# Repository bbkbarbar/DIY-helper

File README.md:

# DIY-helper
..is a arduino based distance meter tool <br> with 4 distance sensors looks "up", "down", left and right, to help positioning things on the wall (e.g.: picture frames) or on the floor.

[The original idea found on this video.](https://youtu.be/QvjQSEvRNkw)

### Planned features:

 - Simple distance measurement
 - Distance measurement in 2 opposite side (can select direction [left-right / up-down])
 - Positioning: continously show the distance values in real time (measure from middle hole or from the side)
    - Can "store" the position and measure distance from that point
 - Area calculation (can select display unit (cm2 or m2 -usefull for wall painting-))

### Used libraries:
 - For handling more push-buttons on 1 single ADC input: [ButtonHandler-library](https://bbkbarbar.github.io/Arduino-ButtonHandler-library/)
 - For handling OLED display over softSpi bus: [SSD1306Ascii-library](https://bbkbarbar.github.io/Arduino-SSD1306Ascii/)
 - For handling HC-SR04 distance sensor: [HC-SR04 library](https://bbkbarbar.github.io/Arduino-HC-SR04-library/)

### Custom modules:
 - Main board (as arduino nano shield) [schematic](https://github.com/bbkbarbar/DIY-helper/blob/master/Docs/mail_board.png), [pcb design](https://github.com/bbkbarbar/DIY-helper/blob/master/Docs/mail_board_pcb.png), [pcb design as .pdf](https://github.com/bbkbarbar/DIY-helper/raw/master/Eagle/DIY_tool_-_Arduino_nano_shield_pcb_v1.1.pdf)
 - Button board [schematic](https://github.com/bbkbarbar/DIY-helper/blob/master/Docs/button_board.png), [pcb design](https://github.com/bbkbarbar/DIY-helper/blob/master/Docs/button_board_pcb.png), [pcb design as .pdf](https://github.com/bbkbarbar/DIY-helper/raw/master/Eagle/DIY_tool_-_button_panel_pcb_v1.pdf)

### ToDo list:
- [x] Clarify / finalyze planned features
- [x] Create test circuits on bread-boards for handling multiple buttons on 1 ADC input
- [x] Try out to use multiple buttons in 1 ADC line
- [x] Create schematic for main board
- [x] Create schematic for button board according to the planned features (e.g.: count of push-buttons)
- [x] Create PCB design for main board
- [x] Create PCB design for button board
- [ ] Finalyze part-list and buy missing parts (if there any)
- [ ] Create test circuits on bread-boards for complete project
- [ ] Create plans for "UI"
- [ ] Create the "RC"-version from firmware
- [ ] <b>After first working bread-board prototype:</b>
- [ ] Create case-design
- [ ] Decide about used materials
- [ ] Build final version in proper case.

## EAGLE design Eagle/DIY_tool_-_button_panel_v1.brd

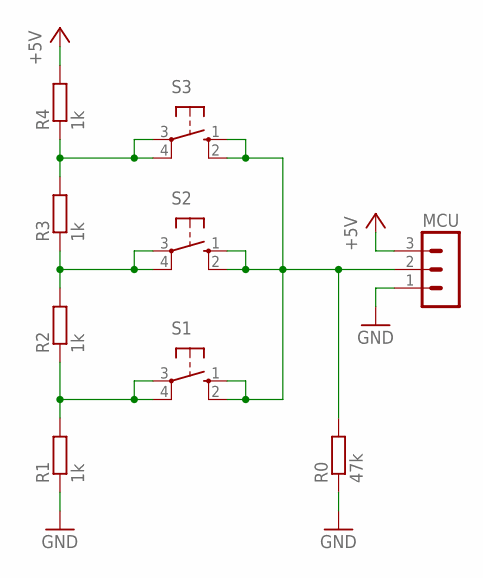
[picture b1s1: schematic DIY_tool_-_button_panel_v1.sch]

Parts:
MCU: MA03-1
R0: 47k; 0207/10
R1, R2, R3, R4: 1k; 0207/10
S1, S2, S3: 10-XX; B3F-10XX

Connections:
+5V: MCU.3, R4.2
ADC: MCU.2, R0.2, S1.1 (S), S1.2 (S1), S2.1 (S), S2.2 (S1), S3.1 (S), S3.2 (S1)
B1: R1.2, R2.1, S1.3, S1.4 (P1)
B2: R2.2, R3.1, S2.3, S2.4 (P1)
B3: R3.2, R4.1, S3.3, S3.4 (P1)
GND: MCU.1, R0.1, R1.1

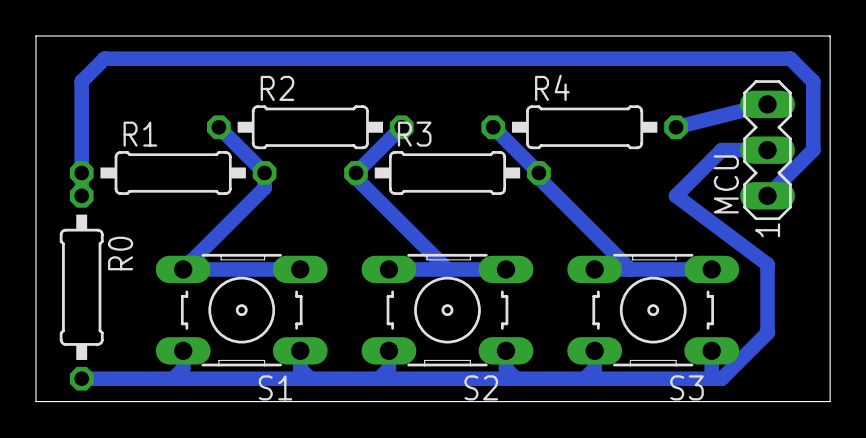
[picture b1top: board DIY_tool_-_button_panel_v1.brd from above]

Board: 2 copper layers, 44.1 x 20.3 mm, 9 parts (0 on the bottom side), 6 nets.

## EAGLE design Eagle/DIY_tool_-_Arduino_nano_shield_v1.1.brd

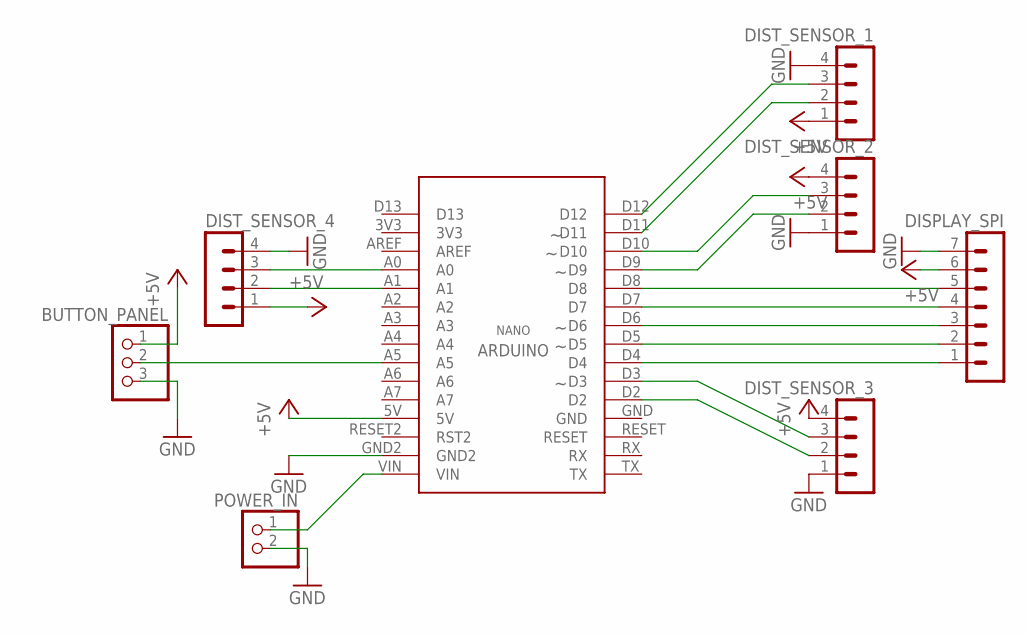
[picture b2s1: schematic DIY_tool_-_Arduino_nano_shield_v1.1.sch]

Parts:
BUTTON_PANEL: PINHD-1X3; 1X03
DISPLAY_SPI: MA07-1
DIST_SENSOR_1, DIST_SENSOR_2, DIST_SENSOR_3, DIST_SENSOR_4: MA04-1
POWER_IN: PINHD-1X2; 1X02
U$2: NANO

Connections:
+5V: BUTTON_PANEL.1, DISPLAY_SPI.6, DIST_SENSOR_1.1, DIST_SENSOR_2.4, DIST_SENSOR_3.4, DIST_SENSOR_4.1, U$2.5V
BTN_IN: BUTTON_PANEL.2, U$2.A5
GND: BUTTON_PANEL.3, DISPLAY_SPI.7, DIST_SENSOR_1.4, DIST_SENSOR_2.1, DIST_SENSOR_3.1, DIST_SENSOR_4.4, POWER_IN.2, U$2.GND2
OLED_CS: DISPLAY_SPI.1, U$2.D4
OLED_D0: DISPLAY_SPI.5, U$2.D8
OLED_D1: DISPLAY_SPI.4, U$2.D7
OLED_DC: DISPLAY_SPI.2, U$2.D5
OLED_RST: DISPLAY_SPI.3, U$2.D6
POWER_IN: POWER_IN.1, U$2.VIN
SENSOR_1_A: DIST_SENSOR_1.3, U$2.D12
SENSOR_1_B: DIST_SENSOR_1.2, U$2.D11
SENSOR_2_A: DIST_SENSOR_2.3, U$2.D10
SENSOR_2_B: DIST_SENSOR_2.2, U$2.D9
SENSOR_3_A: DIST_SENSOR_3.3, U$2.D3
SENSOR_3_B: DIST_SENSOR_3.2, U$2.D2
SENSOR_4_A: DIST_SENSOR_4.3, U$2.A0
SENSOR_4_B: DIST_SENSOR_4.2, U$2.A1

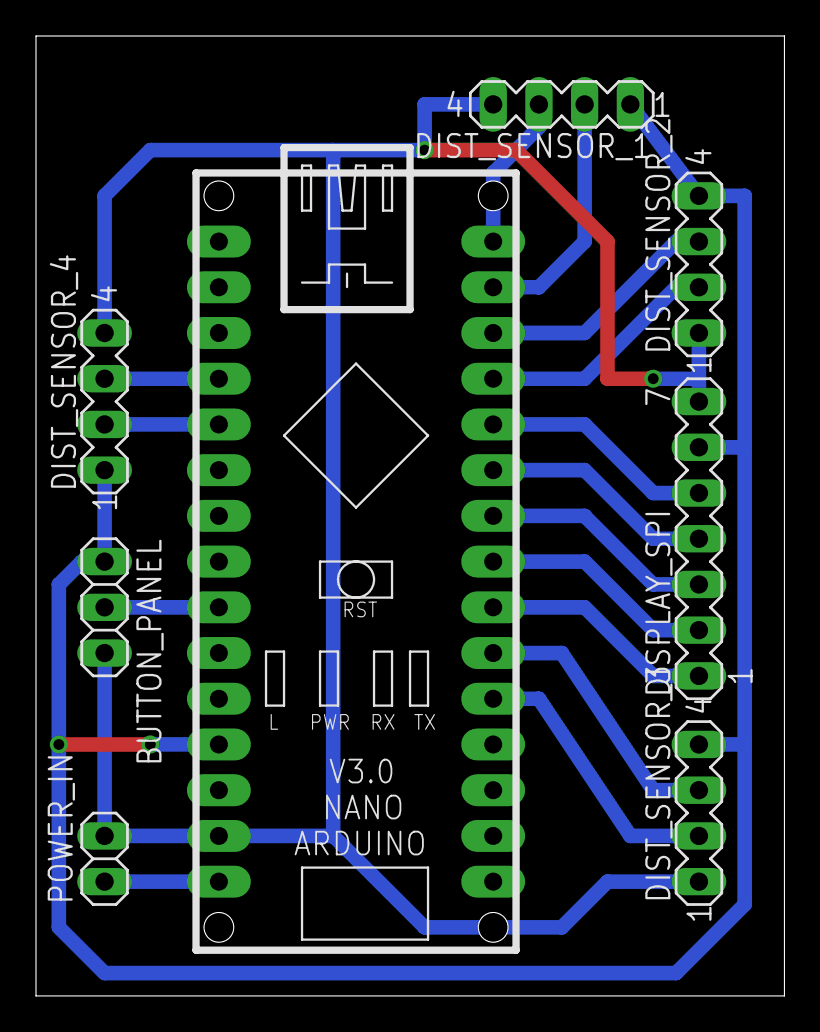
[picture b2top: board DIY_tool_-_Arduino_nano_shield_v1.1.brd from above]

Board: 2 copper layers, 41.6 x 53.3 mm, 8 parts (0 on the bottom side), 17 nets.

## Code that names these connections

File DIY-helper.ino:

#include <buttonhandler.h>

// Pin definitions
//   Display
#define OLED_D0              8
#define OLED_D1              7
#define OLED_RST             6
#define OLED_DC              5
#define OLED_CS              4
  
//   Buttons  
#define ADC_FOR_BUTTONS     A5

//   Disctance sensors


// Buttons
#define NUMBER_OF_BUTTONS    3
#define BTN1                 1
#define BTN2                 2
#define BTN3                 3

// Modes
#define MODE_COUNT           4
#define MODE_SDM             0
#define MODE_OSM             1
#define MODE_POS             2
#define MODE_AREA            3

// Directions
#define DIRECTION_UP         0
#define DIRECTION_RIGHT      1
#define DIRECTION_DOWN       2
#define DIRECTION_LEFT       3

#define DIRECTION_VERTICAL   4
#define DIRECTION_HORIZONTAL 5


#include <SSD1306Ascii.h>
#include <SSD1306AsciiSoftSpi.h>

// Global variables

ButtonHandler buttons;
SSD1306AsciiSoftSpi oled;


// Functions

void setup() {

  buttons.init(ADC_FOR_BUTTONS, NUMBER_OF_BUTTONS);

  oled.begin(&Adafruit128x64, OLED_CS, OLED_DC, OLED_D0, OLED_D1, OLED_RST);
  oled.setFont(Adafruit5x7);
  oled.clear();
  oled.set2X();
  
}


void loop() {



}

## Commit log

2017-02-14 Add plans
2017-02-15 Module_design.xml
2017-02-15 Add basic components.xml
2017-02-15 Added Module_design.xml
2017-02-15 Remove unnamed module-design
2017-02-15 Add partlist, to collect list of needed parts
2017-02-15 Update readme, add ToDo list
2017-02-15 update part list
2017-02-15 Update todo list
2017-02-15 Organize to-do list in series
2017-02-15 Set theme jekyll-theme-architect
2017-02-17 Add links for used libraries
2017-02-18 ToDo list update
2017-02-18 Add first sketch
2017-02-18 Add schematic and pcb design for mainboard
2017-02-18 Add mainboard
2017-02-18 Add used eagle library
2017-02-18 Add library link for disctance sensor
2017-02-19 update partlist
2017-02-19 Add button board schematic and pcb design
2017-02-19 Add lins for button board schematic and pcb design
2017-02-19 Define macros for modes
2017-02-19 Table for finalize modes and button functions
2017-02-19 Add board schematic and pcb design
2017-02-23 Add pcb designs as .pdf
2017-02-23 Add links for pcb design pdfs
